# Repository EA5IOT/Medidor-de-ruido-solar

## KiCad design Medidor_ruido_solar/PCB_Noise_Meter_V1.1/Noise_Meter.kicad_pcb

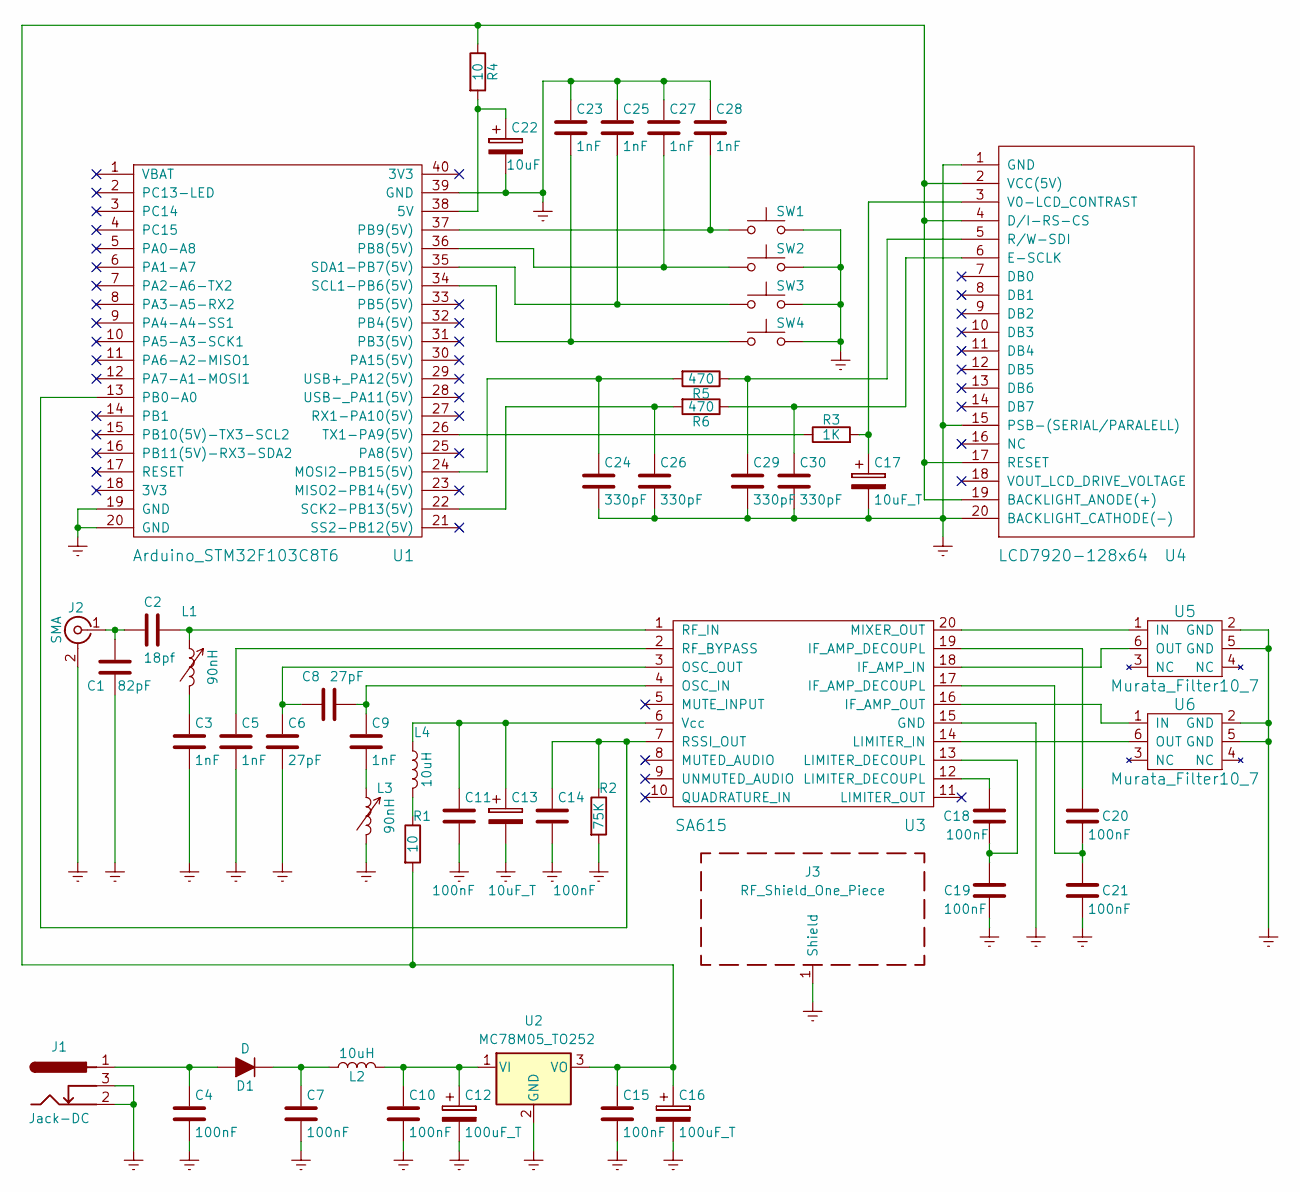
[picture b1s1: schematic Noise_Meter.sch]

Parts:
C1: 82pF; C_0805
C2: 18pf; C_0805
C3, C5, C9, C23, C25, C27, C28: 1nF; C_0805
C4, C7, C10, C11, C14, C15, C18, C19, C20, C21: 100nF; C_0805
C6, C8: 27pF; C_0805
C12, C16: 100uF_T; CP_Tantalum_Case-V_EIA-7343-20_Reflow
C13, C17: 10uF_T; CP_Tantalum_Case-S_EIA-3216-12_Reflow
C22: 10uF; CP_Tantalum_Case-S_EIA-3216-12_Reflow
C24, C26, C29, C30: 330pF; C_0805
D1: D; D_SMB
J1: Jack-DC; JACK_ALIM
J2: SMA; SMA_THT_Jack_Straight
J3: RF_Shield_One_Piece; Laird_Technologies_BMI-S-206-F_36.83x33.68mm
L1, L3: 90nH; L_Neosid_Air-Coil_SML_3turn_HAM0331A
L2, L4: 10uH; L_1812
R1, R4: 10; R_0805
R2: 75K; R_0805
R3: 1K; R_0805
R5, R6: 470; R_0805
SW1, SW2, SW3, SW4: SW_Push; SW_PUSH_6mm_h13mm
U1: Arduino_STM32F103C8T6; DIP-40_W15.24mm
U2: MC78M05_TO252; TO-252-2
U3: SA615; SOIC-20W_7.5x12.8mm_Pitch1.27mm
U4: LCD7920-128x64; AG12864E
U5, U6: Murata_Filter10_7; SOT-23-6_Handsoldering

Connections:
GNDREF: C1.1, C3.2, C4.2, C5.2, C6.2, C7.2, C10.2, C11.2, C12.2, C13.2, C14.2, C15.2, C16.2, C17.2, C19.2, C21.2, C22.2, C23.1, C24.2, C25.1, C26.2, C27.1, C28.1, C29.2, C30.2, J1.2, J1.3, J2.2 (Ext), J3.1, L3.2, R2.2, SW1.2, SW2.2, SW3.2, SW4.2, U1.19 (GND), U1.20 (GND), U1.39 (GND), U2.2 (GND), U3.15 (GND), U4.1 (GND), U4.15 (PSB-(SERIAL/PARALELL)), U4.20 (BACKLIGHT_CATHODE(-)), U5.2 (GND), U5.5 (GND), U6.2 (GND), U6.5 (GND)
unnamed: C1.2, C2.2, J2.1 (In)
unnamed: C2.1, L1.1, U3.1 (RF_IN)
unnamed: C3.1, L1.2
unnamed: C4.1, D1.2 (A), J1.1
unnamed: C5.1, U3.2 (RF_BYPASS)
unnamed: C6.1, C8.2, U3.3 (OSC_OUT)
unnamed: C7.1, D1.1 (K), L2.1
unnamed: C8.1, C9.1, U3.4 (OSC_IN)
unnamed: C9.2, L3.1
unnamed: C10.1, C12.1, L2.2, U2.1 (VI)
unnamed: C11.1, C13.1, L4.1, U3.6 (Vcc)
unnamed: C14.1, R2.1, U1.13 (PB0-A0), U3.7 (RSSI_OUT)
unnamed: C15.1, C16.1, R1.2, R4.1, U2.3 (VO), U4.2 (VCC(5V)), U4.4 (D/I-RS-CS), U4.17 (RESET), U4.19 (BACKLIGHT_ANODE(+))
unnamed: C17.1, R3.2, U4.3 (V0-LCD_CONTRAST)
unnamed: C18.1, C19.1, U3.13 (LIMITER_DECOUPL)
unnamed: C18.2, U3.12 (LIMITER_DECOUPL)
unnamed: C20.1, U3.19 (IF_AMP_DECOUPL)
unnamed: C20.2, C21.1, U3.17 (IF_AMP_DECOUPL)
unnamed: C22.1, R4.2, U1.38 (5V)
unnamed: C23.2, SW4.1, U1.34 (SCL1-PB6(5V))
unnamed: C24.1, R5.2, U1.24 (MOSI2-PB15(5V))
unnamed: C25.2, SW3.1, U1.35 (SDA1-PB7(5V))
unnamed: C26.1, R6.2, U1.22 (SCK2-PB13(5V))
unnamed: C27.2, SW2.1, U1.36 (PB8(5V))
unnamed: C28.2, SW1.1, U1.37 (PB9(5V))
unnamed: C29.1, R5.1, U4.5 (R/W-SDI)
unnamed: C30.1, R6.1, U4.6 (E-SCLK)
unnamed: L4.2, R1.1
unnamed: R3.1, U1.26 (TX1-PA9(5V))
unnamed: U3.14 (LIMITER_IN), U6.6 (OUT)
unnamed: U3.16 (IF_AMP_OUT), U6.1 (IN)
unnamed: U3.18 (IF_AMP_IN), U5.6 (OUT)
unnamed: U3.20 (MIXER_OUT), U5.1 (IN)

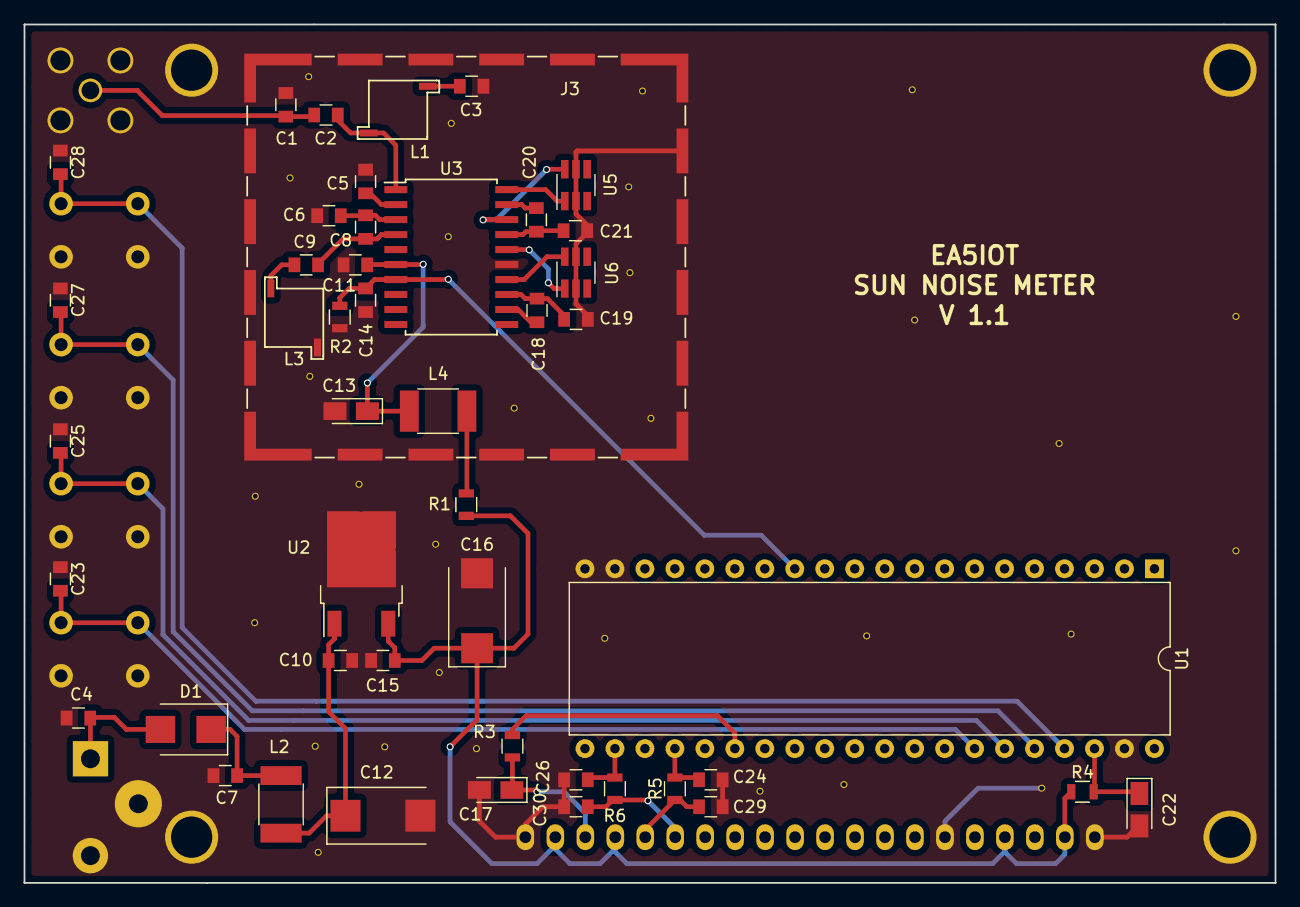
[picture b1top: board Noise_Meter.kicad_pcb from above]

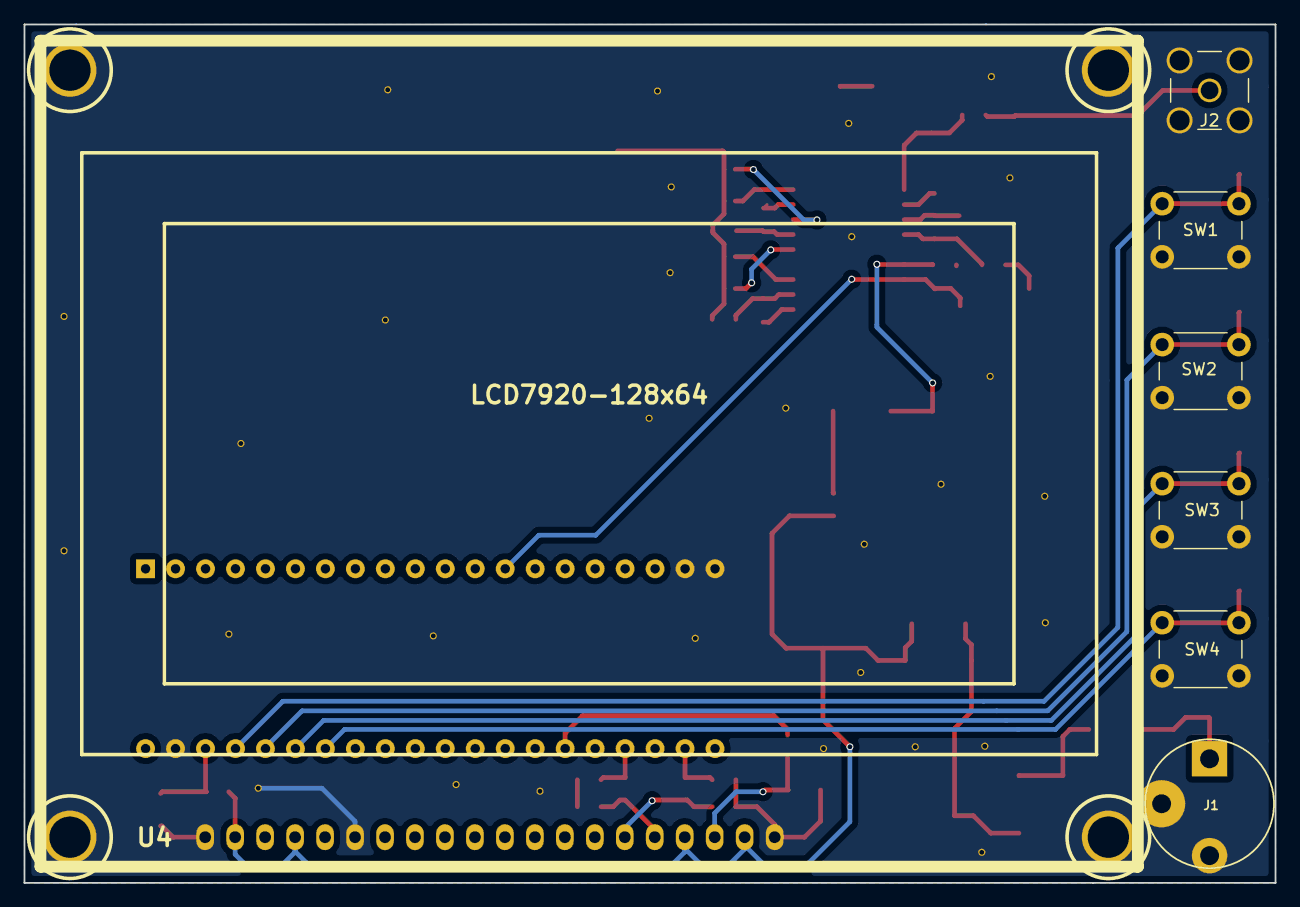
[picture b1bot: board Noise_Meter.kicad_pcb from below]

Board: 2 copper layers, 106.0 x 72.7 mm, 54 parts (7 on the bottom side), 34 nets.

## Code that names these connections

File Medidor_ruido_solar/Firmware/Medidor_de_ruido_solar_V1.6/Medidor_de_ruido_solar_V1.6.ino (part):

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extern const PROGMEM LcdFont font5x7_STM;                                                                   // in glcd10x10.cpp

#define LCD_USE_SPI     (false)                                                                             // no SPI yet for STM32
#define MOSIpin         PB15
#define SCLKpin         PB13
#define LED             PC13
#define Boton1          PB9
#define Boton2          PB8
#define Boton3          PB7
#define Boton4          PB6
#define ADC             PB0
#define Timer1Ch2       PA9                                                                                 // Salida PWM para el control de la retroiluminación de la pantalla, PA9 pwm 5V out (open drain)
#define Y0              13                                                                                  // inicio escala
#define Y1              21                                                                                  // valores escala

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  pinMode(Timer1Ch2, PWM);                                                                                  // No hay manera de acceder al registro BDTR para activar el OUTPUT COMPARE, asi hace lo mismo
  TIMER1->regs.gen->CCR2 = Contraste * 256;                                                                 // PWM para controlar el contraste de la pantalla
  GPIOA->regs->CRH &= 0xFFFFFF3F;                                                                           // Se hace un and para poner los ceros
  GPIOA->regs->CRH |= 0x000000C0;                                                                           // Se hace un or para poner los unos, alternate function open drain PA9 para PWM de 5V
  TIMER1->regs.gen->CR1 = 0x0001;                                                                           // Se habilita el contador para que genere el PWM

  return;
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
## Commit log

2018-09-17 Fotos y Videos
2018-10-27 VideoManual
    VideoManual
2018-11-03 Cargador_Bateria_Litio
    Cargador_Bateria_litio
2018-11-03 Medidor_Ruido_Solar
    Cargador Balanceador
2018-11-03 Medidor_Ruido_Solar
2018-11-03 Medidor_Ruido_Solar
    Medidor_Ruido_Solar
2018-11-18 Cargador Balanceador
    Cargador Balanceador
2019-01-26 BOM updated
2019-01-30 Update Medidor_ruido_solar/Firmware/Medidor_de_ruido_solar_V1.6/Medidor_de_ruido_solar_V1.6.ino
    Medidor de ruido solar
2019-02-19 Medidor Ruido Solar
    Presentacion
2019-04-04 Create Medidor_de_ruido_solar_V1.7.ino
    2db calibration points
2019-04-29 Track 17 files into repository.
    - modified LICENSE
    - modified Medidor_ruido_solar/Cargador_Balanceador/Cargador_Balanceador-cache.lib
    - modified Medidor_ruido_solar/Cargador_Balanceador/Cargador_Balanceador-rescue.lib
    - modified Medidor_ruido_solar/Cargador_Balanceador/Cargador_Balanceador.bak
    - modified Medidor_ruido_solar/Cargador_Balanceador/Cargador_Balanceador.pro
    - modified Medidor_ruido_solar/Cargador_Balanceador/Cargador_Balanceador.sch
2019-04-29 Creates README.md
    Auto commit by GitBook Editor
2019-04-29 Updates README.md
    Auto commit by GitBook Editor
2019-04-29 Track 3 files into repository.
    - removed assets/import.png
    - removed assets/Presentacion2.jpg
    - modified README.md
    Auto commit by GitBook Editor
2019-10-11 Version 2.0
    Version 2.0
2019-10-16 Version 2.1
    Version 2.1

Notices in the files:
Medidor_ruido_solar/Firmware/Medidor_de_ruido_solar_V1.6/Medidor_de_ruido_solar_V1.6.ino:
Copyright (C) 2018  EA5IOT
This program is free software: you can redistribute it and/or modify
it under the terms of the GNU General Public License as published by
the Free Software Foundation, either version 3 of the License, or
(at your option) any later version.
